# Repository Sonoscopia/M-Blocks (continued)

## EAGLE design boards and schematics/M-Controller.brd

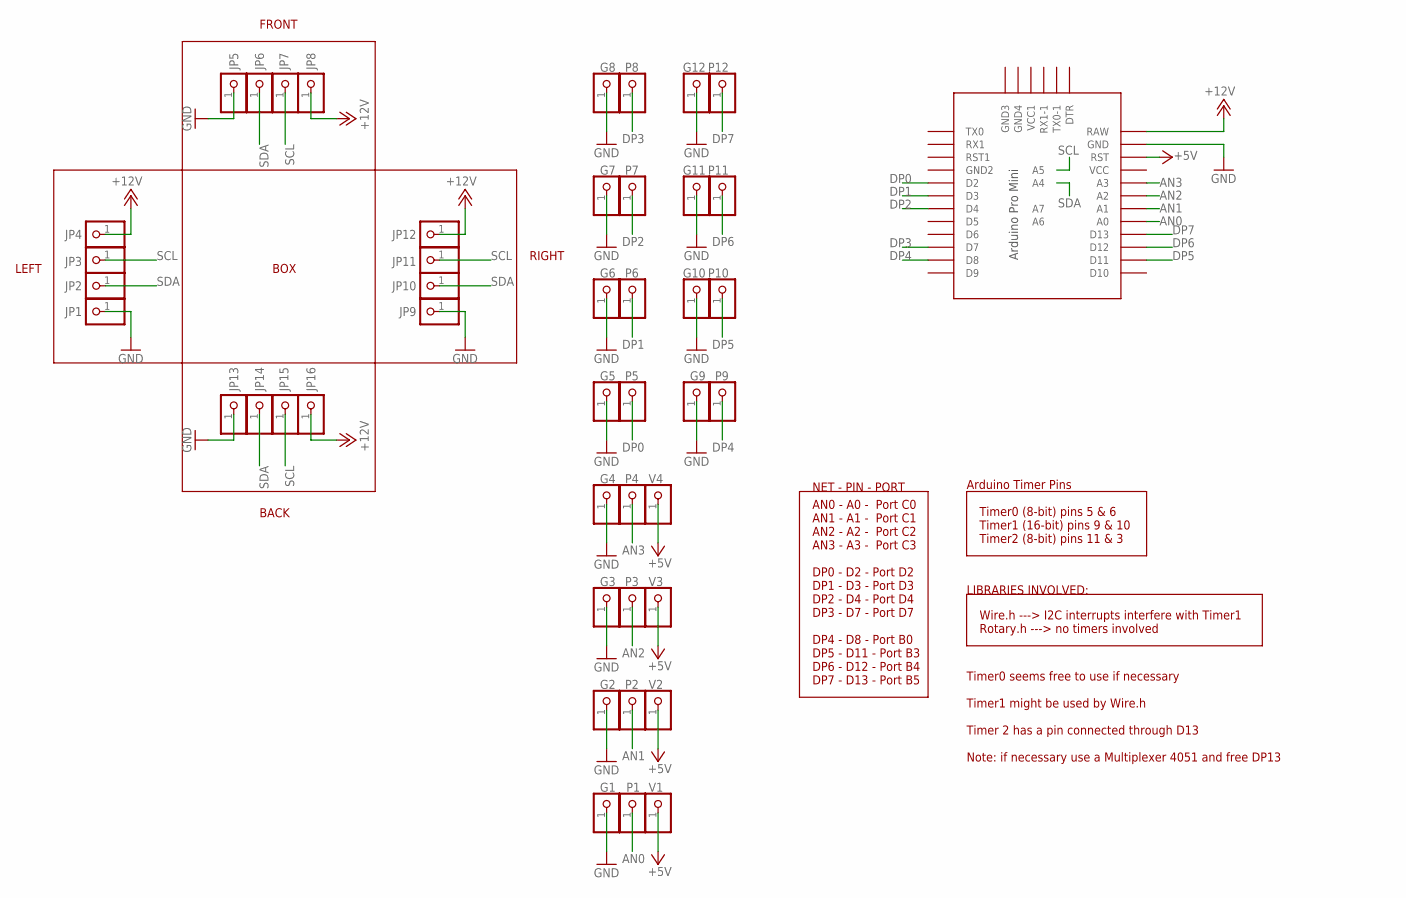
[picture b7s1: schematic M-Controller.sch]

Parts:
G1, G2, G3, G4, G5, G6, G7, G8, G9, G10, G11, G12: PINHD-1X1; 1X01
JP1, JP2, JP3, JP4, JP5, JP6, JP7, JP8, JP9, JP10, JP11, JP12, JP13, JP14, JP15, JP16: PINHD-1X1; 1X01
P1, P2, P3, P4, P5, P6, P7, P8, P9, P10, P11, P12: PINHD-1X1; 1X01
U$1: PRO-MINI-2
V1, V2, V3, V4: PINHD-1X1; 1X01

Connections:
+5V: U$1.RST, V1.1, V2.1, V3.1, V4.1
+12V: JP4.1, JP8.1, JP12.1, JP16.1, U$1.RAW
AN0: P1.1, U$1.A0
AN1: P2.1, U$1.A1
AN2: P3.1, U$1.A2
AN3: P4.1, U$1.A3
DP0: P5.1, U$1.D2
DP1: P6.1, U$1.D3
DP2: P7.1, U$1.D4
DP3: P8.1, U$1.D7
DP4: P9.1, U$1.D8
DP5: P10.1, U$1.D11
DP6: P11.1, U$1.D12
DP7: P12.1, U$1.D13
GND: G1.1, G2.1, G3.1, G4.1, G5.1, G6.1, G7.1, G8.1, G9.1, G10.1, G11.1, G12.1, JP1.1, JP5.1, JP9.1, JP13.1, U$1.GND
SCL: JP3.1, JP7.1, JP11.1, JP15.1, U$1.A5
SDA: JP2.1, JP6.1, JP10.1, JP14.1, U$1.A4

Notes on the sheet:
Timer0 (8-bit) pins 5 & 6 Timer1 (16-bit) pins 9 & 10 Timer2 (8-bit) pins 11 & 3
Arduino Timer Pins
AN0 - A0 - Port C0 AN1 - A1 - Port C1 AN2 - A2 - Port C2 AN3 - A3 - Port C3 DP0 - D2 - Port D2 DP1 - D3 - Port D3 DP2 - D4 - Port D4 DP3 - D7 - Port D7 DP4 - D8 - Port B0 DP5 - D11 - Port B3 DP6 - D12 - Port B4 DP7 - D13 - Port B5
Wire.h ---> I2C interrupts interfere with Timer1 Rotary.h ---> no timers involved
LIBRARIES INVOLVED:
NET - PIN - PORT
Timer0 seems free to use if necessary Timer1 might be used by Wire.h Timer 2 has a pin connected through D13 Note: if necessary use a Multiplexer 4051 and free DP13
BOX
FRONT
RIGHT
LEFT
BACK

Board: 2 copper layers, 45 parts (0 on the bottom side), 17 nets, no tracks yet.

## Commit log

2019-08-08 controller schematic first sketch
2019-08-08 minor schematic update
2019-08-08 replaced 5v input to 12V input onto the RAW pin
    12V is more consistent than 5V to "spread" between several modules
2019-08-08 minor change
2019-08-14 added default gitignore file
2019-08-14 added example for super fast encoder reading
2019-08-14 updated schematic
    - noted timer and library issues
    - added all 4 TRRS connectors
    - mapped all I/O
2019-08-22 minor changes
2019-08-22 changed board sized and fixed drill holes
2019-08-22 uploaded M-Toggle
    Veroboard version
    Revision 1
2019-08-22 changed spacing in digital connectors
    the molex connectors would not fit
2019-08-22 toggle board minor changes
2019-08-24 added tester code for TOGGLE module
2019-08-24 minor fix
2019-08-24 moved to examples folder
2019-08-24 First simple working version
    Controller as Slave Sender
    Brain as Master Receiver
2019-08-24 forgot to save :)
2019-08-24 version 0.0.2
    Inverted Master/Slave relationship.
    Now M-Brain is the slave and M-Controllers are masters.
    This way the controllers send data whenever their hardware sensor data
    changes, while the slave (M-Brain) is requested to read this data.
2019-08-24 minor fixes
2019-08-24 simple working version
    - reads M-Toggle switches and sends MIDI
    - implemented encoder reading and conversion to 7leds with binary
    representation
2019-08-24 moved sketches to firmware/Arduino
    this folder should contain working versions of the code in
    firmware/Atmel
2019-08-25 updated gitignore because of Atmel Studio
2019-08-25 moved M-Brain to Atmel Studio IDE
2019-08-25 implemented NOTEMAP and VELMAP functions
2019-08-25 starting to work with EEPROM
    storing presets
2019-08-25 added I2C receiver test
2019-08-25 error in a comment
2019-08-25 now able to save machine state
    although there are still some issues (see issues)
2019-08-25 notemap and velocity map properly implemented
    code could still be more efficient, but lets leave that for later...
2019-08-25 uploaded M-Button code
2019-08-25 minor change
    creation data update
2019-08-25 added some potentiometer smoothing examples
2019-08-25 super simple sketch to print potentiometer values
2019-08-25 uploaded M-Knob controller sketch
2020-07-15 added TO_DO file
2020-07-15 added rotary encoder snippet
2020-07-15 significant changes to M-Brain
    Changed the TRRS jack connection diagram in order to avoid short circuits
2020-07-15 organized schematics in a folder structure
    now every controller has its own folder
2020-08-24 Updated m-controller template
    changes:
    - there was an error in the arduino pro library part, so a library was
    made in order to edit this part
    - added molex connectors
2020-10-26 uploaded case design files
2020-10-26 uploaded connection diagrams
2020-10-26 changed TRRS connections
    plus added Molex connectors like the ones I'm using in hardware
2020-10-26 (eagle:removed lock)
2020-10-27 M-toggle new circuit version
    for the smaller v2 cases
2020-11-06 corrected mistake
    +5V was connected to RST instead of VCC
2020-11-06 uploaded M-Knob
2020-11-06 added TRRS connection diagram between modules
2020-11-08 reorganized 'testers' folder
    'topics' subfolder contains tester sketches for several topics while
    MController testers are kept on the 'testers' root directory
2020-11-08 added MToggle tester
2020-11-08 set DEBUG back to 0
2020-11-08 removed MController tester
    MController testers are redundant since the firmware allows to set a
    DEBUG variable which will print hardware state
2020-11-10 doc moving to v0.1.0
    moving from v.0.0.3 to v0.1.0
    almost there to functional prototype
2020-11-10 trying to fix git problems
2020-11-10 minor
2020-11-10 reorganized docs
2020-11-12 added M-Controllers address list according to v0.1.0
2020-11-12 updated M-Toggle to version 0.1.0
2020-11-12 updated M-Knob to version 0.1.0
2020-11-12 minor correction
2020-11-13 added some utilities
2020-11-13 added snippet
2020-11-13 added useful bitwise op table
2020-11-13 moving to version 0.1.0
    - first working version with only PLAY MODE and NOTE MAP implemented
2020-11-13 output value change
    change output to 127 if button is on
2020-11-13 implemented other map functions
    mapping functions implemented:
    - note (implemented in previous commit)
    - velocity
    - CC
    - CH
    - set global channel
2020-11-13 added tester
    test encoder rotation and led's on M-Brain boards
2020-11-13 implemented load and save functions
2020-11-13 removed file
2020-11-13 ported Atmel version to Arduino IDE
2020-11-15 updated manual
2020-11-15 added MIDI debugger tool in MaxMSP
2020-12-16 minor change
    changed vertical measure to inches because it's easier to count the
    holes in the veroboard to cut
2020-12-16 added M-Button schematic and board
2020-12-16 updated M-address list
2020-12-17 added M-Fader schematic and board
2020-12-18 added M-Fader firmware
2020-12-18 M-Controller template Revision B
    changed board because of M-Encoder since the encoders have RC filters to
    improve readings and these components wouldn't fit on the board and
    would break compatibility between different M-Controller boards.
    M-Encoder has a 2nd board containing the RC filters.
2020-12-21 added Encoder-C board and schematic
2020-12-23 Revert "minor changes"
    This reverts commit 44245df26b32f1cf179dd13bb4aecd7d2b900a5f.
2020-12-23 Revert "Revert "minor changes""
    This reverts commit ba90e9202e971c0db24de2081c5a6a48891d21ff.
2020-12-23 added M-TrackPad board and schematic
2021-06-13 minor change
    changed debug baud rate to keep equal specs across devices (M-Brain and
    all M-Controllers print at 115200 baudrate when in debug mode)
2021-06-13 minor changes
    corrected some comment mistakes
2021-06-13 added M-Joystick
    The potentiometers on this Sparkfun joystick aren't as good as the
    Bourns potentiometers on M-Knob, giving some 'false' readings. An
    exponential smoothing algorithm was implemented to address this issue.
2021-06-13 MButton debounce
    added debounce to avoid unwanted triggers
2021-06-13 updated gitinore
    ignoring all folders starting with underscore (_folder)
2021-06-13 MToggle debounce
    added debounce to avoid unwanted triggers
2021-06-13 global channel fix
    fixed a mistake: MIDI messages were always sent to the global channel
    even if a controller mapping was set to a different channel
2021-06-13 EEPROM improvement
    replaced all write() functions by update() which only changes the
    variable in the EEPROM if it differs from the previously stored data,
    thus improving EEPROM lifespan
2021-06-13 added some EEPROM utilities
    easy sketches for reading the entire EEPROM and resetting it to default
    M-Brain values
2021-06-13 added definitions
    used to simplify the preset reset procedure
2021-06-13 variable type changes
    these changes do not alter the functioning of the actual code but makes
    it easier to understand the code
2021-06-13 fixed issues #6 and #7
    fixed issues #6 and #7
    as is the code is still very messy
    cleanup and performance will be addressed in the following commits
2021-06-13 removed debug function + some cleanup
    - removed debug function: we can debug using MIDI, there's no actual
    need for (another) serial debug
    - minor fixes but there are still some bugs when mapping controllers
2021-06-14 mapping is working but....
    when mapping another controller, LEDS show the last triggered controller
    mapping instead of blinking to indicate it's ready to map....this was
    not intended and I'm not really sure right now why this is happening but
    it can actually be useful....
    If we press LOAD/CANCEL before mapping the LEDS blink as intended !
2021-06-14 updated README and TO DO
2021-06-14 updated TO DO
2021-06-14 added MADDR for M-Enc-C1 and M-Enc-D1
2021-06-14 added sketch to test M-Encoder hardware
2021-06-14 starting M-Encoder-C atmel studio project
2021-06-15 updated TO DO list
2021-06-15 cleanup
2021-06-15 implemented encoder+button modes stored to EEPROM
2021-06-15 implemented mode1 and mode2
    mode1 and mode2 have different encoder increments if the encoder button
    is pressed while turning the encoder
2021-06-15 implemented mode3
    in this mode the encoder button acts as a toggle, toggling (ahah)
    between 0 and 127
2021-06-15 implemented mode4
    In this mode the encoder button presses are treated like a MIDI note and
    are sent to a different addres, so the encoders can still be used to map
    CC events
2021-06-15 upload iqs550_arduino_example starting M-Trackpad
    just uploaded the example provided by Azoteq
    notes:
    - could not upload using Arduino IDE, only Atmel Studio...
    - uploaded the code but couldn't get useful data: an error message was
    constantly printed
    - this is way too complex at 4 AM with too little sleep
2023-02-04 fixed note played
    notes played were only programmed for full velocity
    (guess I wasn't expecting continuous controls like knobs to play notes, but now they can)
2023-02-04 this was made specifically to work w/ PHOBOS
    this could actually be a mode (see modes on M-Enc).....
2023-02-04 incremented version
2023-02-05 Update MJoystick.ino
    minor changes
2023-02-05 Create mblocks.midi.inspector.maxpat
    added MIDI inspector for MaxMSP
    should compile app for both MacOS and Windows
2023-02-05 Create MJoystick4D.ino
    moded MJoystick to send 4 different values (x+, x-, y+, y-) instead of just x and y
    this was made specifically for Phobos
    in a normal MIDI context this doesn't make sense (think, for example, of Ableton's XY controllers)
2024-11-08 important notes
    Added notes in the beginning of M-Brain firmware and repos README:
    When programming an M-Brain for the first time do not forget to set the EEPROM memory using /utilities/EEPROM_Preset_Clear/
2024-11-08 added mappings for Sonos projects
2024-11-08 Update Phobos installation version_v1.md
    minor change
2025-08-14 Create LICENSE
